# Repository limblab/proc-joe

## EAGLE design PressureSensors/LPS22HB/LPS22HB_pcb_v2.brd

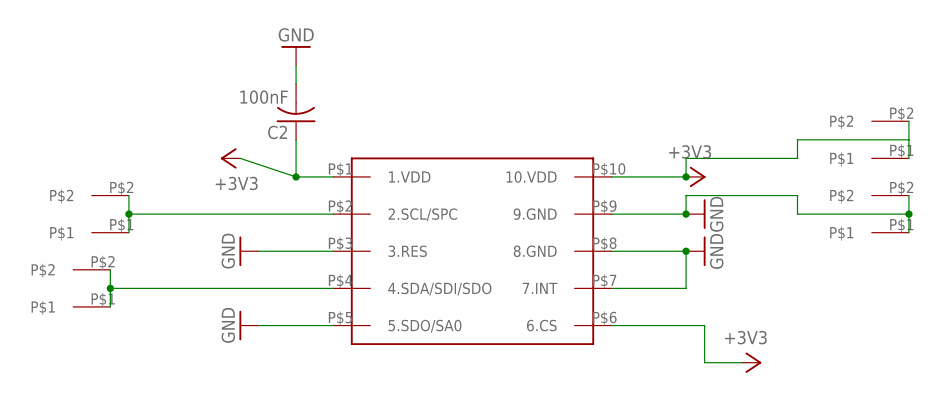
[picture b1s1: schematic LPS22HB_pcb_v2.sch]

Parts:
C2: 100nF; C0402
U$1: LPS22HB_HLGA
U$2, U$3, U$4, U$5: WIREPAD_PADWIREPAD_0,6/0,4_PAD; WIREPAD_0,6/0,4_PAD

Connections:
+3V3: C2.1, U$1.P$1 (1.VDD), U$1.P$6 (6.CS), U$1.P$10 (10.VDD), U$5.P$1, U$5.P$2
GND: C2.2, U$1.P$3 (3.RES), U$1.P$5 (5.SDO/SA0), U$1.P$7 (7.INT), U$1.P$8 (8.GND), U$1.P$9 (9.GND), U$4.P$1, U$4.P$2
unnamed: U$1.P$2 (2.SCL/SPC), U$2.P$1, U$2.P$2
unnamed: U$1.P$4 (4.SDA/SDI/SDO), U$3.P$1, U$3.P$2

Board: 2 copper layers, 6 parts (5 on the bottom side), 4 nets, no tracks yet.

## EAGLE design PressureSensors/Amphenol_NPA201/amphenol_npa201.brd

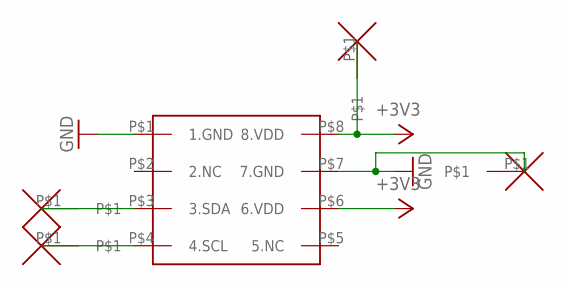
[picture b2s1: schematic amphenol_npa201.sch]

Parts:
U$1: AMPHENOL_NPA201
U$2, U$3, U$4, U$5: WIREPAD_0,8/0,45

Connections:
+3V3: U$1.P$6 (6.VDD), U$1.P$8 (8.VDD), U$4.P$1
GND: U$1.P$1 (1.GND), U$1.P$7 (7.GND), U$5.P$1
unnamed: U$1.P$3 (3.SDA), U$2.P$1
unnamed: U$1.P$4 (4.SCL), U$3.P$1

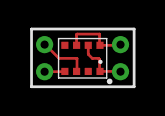
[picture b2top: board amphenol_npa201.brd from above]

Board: 2 copper layers, 5 parts (0 on the bottom side), 4 nets.

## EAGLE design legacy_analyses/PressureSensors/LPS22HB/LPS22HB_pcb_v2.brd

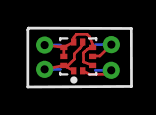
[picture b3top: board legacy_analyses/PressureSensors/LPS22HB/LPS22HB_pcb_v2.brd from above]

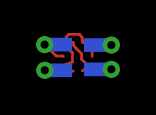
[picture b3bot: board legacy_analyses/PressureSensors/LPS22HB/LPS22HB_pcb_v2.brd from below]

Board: 2 copper layers, 5 parts (4 on the bottom side), 4 nets.

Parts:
U1: LPS22HB; LGA10R50P2X3_200X200X80
U$1, U$2, U$6, U$7: WIREPAD_PADWIREPAD_0,6/0,4_PAD; WIREPAD_0,6/0,4_PAD

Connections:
+3V3: U1.1, U1.6, U1.10, U$1.P$1, U$1.P$2
GND: U1.3, U1.5, U1.7, U1.8, U1.9, U$2.P$1, U$2.P$2
unnamed: U1.2, U$6.P$1, U$6.P$2
unnamed: U1.4, U$7.P$1, U$7.P$2

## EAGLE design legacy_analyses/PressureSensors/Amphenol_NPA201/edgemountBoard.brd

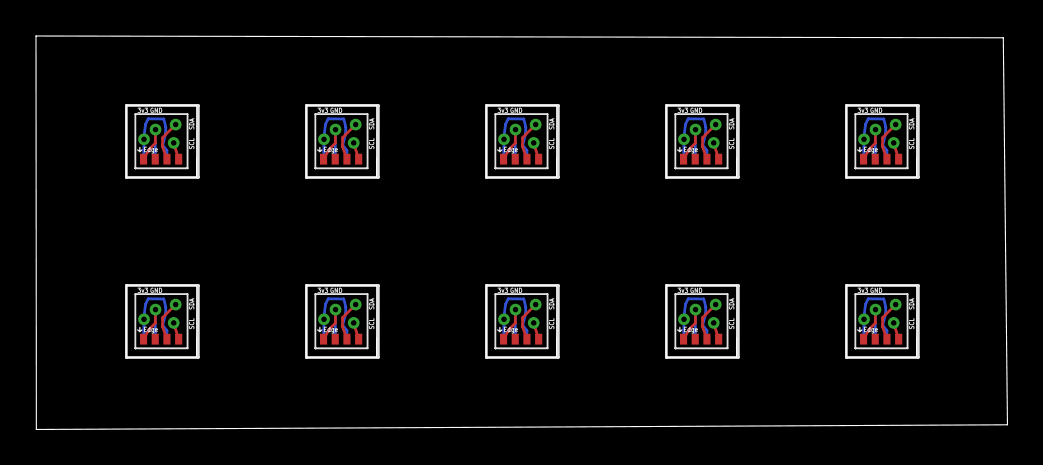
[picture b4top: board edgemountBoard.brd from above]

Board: 2 copper layers, 54.0 x 21.9 mm, 50 parts (0 on the bottom side), 40 nets.

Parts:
U$1, U$6, U$11, U$16, U$21, U$26, U$31, U$36, U$41, U$46: AMPHENOL_NPA201EDGEMOUNT; AMPHENOL_NPA201_EDGEMOUNT
U$2, U$3, U$4, U$5, U$7, U$8, U$9, U$10, U$12, U$13, U$14, U$15, U$17, U$18, U$19, U$20, U$22, U$23, U$24, U$25, U$27, U$28, U$29, U$30, U$32, U$33, U$34, U$35, U$37, U$38, U$39, U$40, U$42, U$43, U$44, U$45, U$47, U$48, U$49, U$50: WIREPADWIREPAD_0,5/0,3; WIREPAD_0,5/0,3

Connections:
+3V1: U$6.P$6, U$6.P$8, U$10.P$1
+3V2: U$11.P$6, U$11.P$8, U$15.P$1
+3V3: U$1.P$6, U$1.P$8, U$5.P$1
+3V4: U$16.P$6, U$16.P$8, U$20.P$1
+3V5: U$21.P$6, U$21.P$8, U$25.P$1
+3V6: U$26.P$6, U$26.P$8, U$30.P$1
+3V7: U$31.P$6, U$31.P$8, U$35.P$1
+3V8: U$36.P$6, U$36.P$8, U$40.P$1
+3V9: U$41.P$6, U$41.P$8, U$45.P$1
+3V10: U$46.P$6, U$46.P$8, U$50.P$1
GND: U$1.P$1, U$1.P$7, U$4.P$1
GND1: U$6.P$1, U$6.P$7, U$9.P$1
GND2: U$11.P$1, U$11.P$7, U$14.P$1
GND3: U$16.P$1, U$16.P$7, U$19.P$1
GND4: U$21.P$1, U$21.P$7, U$24.P$1
GND5: U$26.P$1, U$26.P$7, U$29.P$1
GND6: U$31.P$1, U$31.P$7, U$34.P$1
GND7: U$36.P$1, U$36.P$7, U$39.P$1
GND8: U$41.P$1, U$41.P$7, U$44.P$1
GND9: U$46.P$1, U$46.P$7, U$49.P$1
unnamed: U$1.P$3, U$2.P$1
unnamed: U$1.P$4, U$3.P$1
unnamed: U$6.P$3, U$7.P$1
unnamed: U$6.P$4, U$8.P$1
unnamed: U$11.P$3, U$12.P$1
unnamed: U$11.P$4, U$13.P$1
unnamed: U$16.P$3, U$17.P$1
unnamed: U$16.P$4, U$18.P$1
unnamed: U$21.P$3, U$22.P$1
unnamed: U$21.P$4, U$23.P$1
unnamed: U$26.P$3, U$27.P$1
unnamed: U$26.P$4, U$28.P$1
unnamed: U$31.P$3, U$32.P$1
unnamed: U$31.P$4, U$33.P$1
unnamed: U$36.P$3, U$37.P$1
unnamed: U$36.P$4, U$38.P$1
unnamed: U$41.P$3, U$42.P$1
unnamed: U$41.P$4, U$43.P$1
unnamed: U$46.P$3, U$47.P$1
unnamed: U$46.P$4, U$48.P$1

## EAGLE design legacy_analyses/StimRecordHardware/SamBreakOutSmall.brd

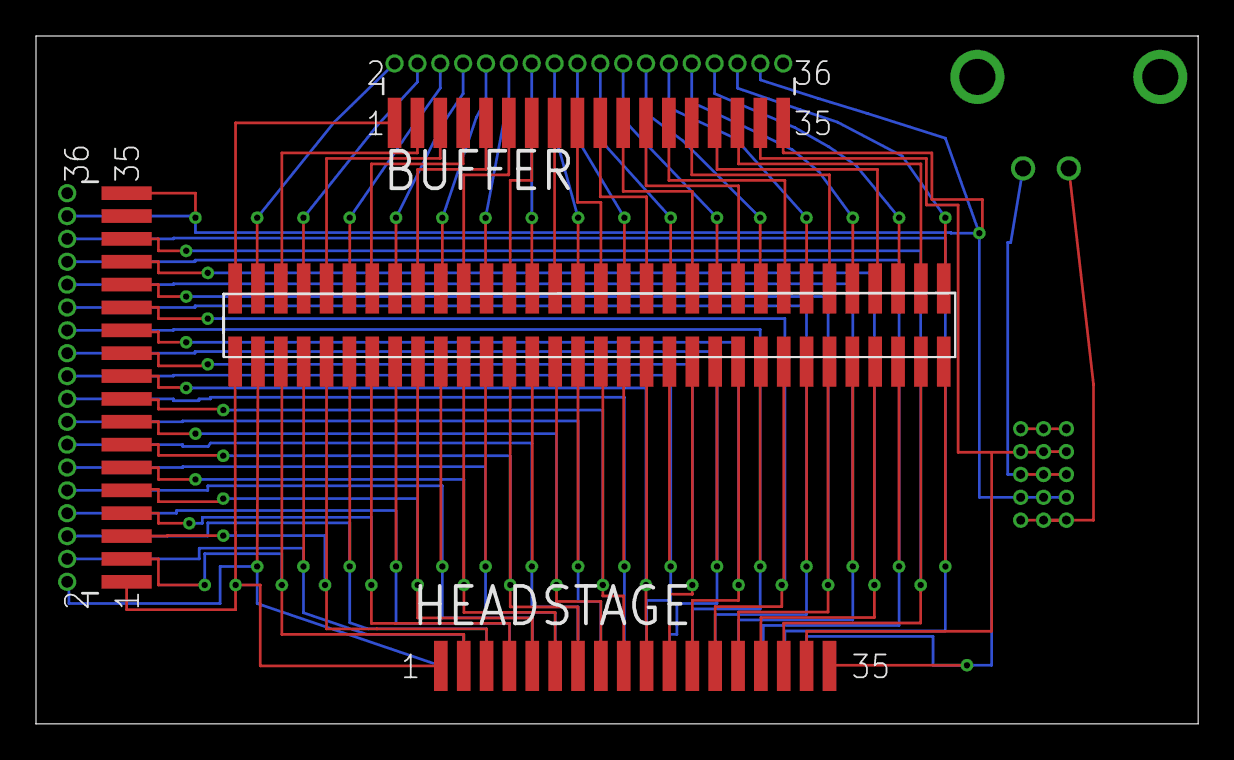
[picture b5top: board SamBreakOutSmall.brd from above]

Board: 2 copper layers, 64.6 x 38.2 mm, 8 parts (0 on the bottom side), 69 nets.

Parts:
BUFFER: FTSH-118-01-L-MTREGULAR; FTSH-118-01-L-MT
HEADSTAGE: SFMC-118-L1-S-D
STIM: FTSH-118-01-L-MTREGULAR; FTSH-118-01-L-MT
U$1: BNCRAMOUNT
U$3: FTSH-132-01-L-DV; FTSH-132-01-DV
U$34, U$35, U$36: LPPB051NFFN-RC

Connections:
0V: BUFFER.33, HEADSTAGE.33, U$34.P$2, U$35.P$2, U$36.P$2
GND: BUFFER.34, BUFFER.35, HEADSTAGE.34, HEADSTAGE.35, STIM.34, STIM.35, U$34.P$4, U$35.P$4, U$36.P$4
unnamed: BUFFER.1, U$3.2
unnamed: BUFFER.29, U$3.58
unnamed: BUFFER.3, U$3.6
unnamed: BUFFER.2, U$3.4
unnamed: BUFFER.5, U$3.10
unnamed: BUFFER.7, U$3.14
unnamed: BUFFER.9, U$3.18
unnamed: BUFFER.11, U$3.22
unnamed: BUFFER.13, U$3.26
unnamed: BUFFER.15, U$3.30
unnamed: BUFFER.17, U$3.34
unnamed: BUFFER.19, U$3.38
unnamed: BUFFER.27, U$3.54
unnamed: BUFFER.23, U$3.46
unnamed: BUFFER.25, U$3.50
unnamed: BUFFER.4, U$3.8
unnamed: BUFFER.6, U$3.12
unnamed: BUFFER.31, U$3.62
unnamed: BUFFER.8, U$3.16
unnamed: BUFFER.10, U$3.20
unnamed: BUFFER.12, U$3.24
unnamed: BUFFER.14, U$3.28
unnamed: BUFFER.16, U$3.32
unnamed: BUFFER.18, U$3.36
unnamed: BUFFER.20, U$3.40
unnamed: BUFFER.21, U$3.42
unnamed: BUFFER.22, U$3.44
unnamed: BUFFER.24, U$3.48
unnamed: BUFFER.26, U$3.52
unnamed: BUFFER.28, U$3.56
unnamed: BUFFER.30, U$3.60
unnamed: BUFFER.32, U$3.64
unnamed: HEADSTAGE.3, STIM.3, U$3.5
unnamed: HEADSTAGE.5, STIM.5, U$3.9
unnamed: HEADSTAGE.7, STIM.7, U$3.13
unnamed: HEADSTAGE.9, STIM.9, U$3.17
unnamed: HEADSTAGE.11, STIM.11, U$3.21
unnamed: HEADSTAGE.13, STIM.13, U$3.25
unnamed: HEADSTAGE.15, STIM.15, U$3.29
unnamed: HEADSTAGE.17, STIM.17, U$3.33
unnamed: HEADSTAGE.19, STIM.19, U$3.37
unnamed: HEADSTAGE.21, STIM.21, U$3.41
unnamed: HEADSTAGE.23, STIM.23, U$3.45
unnamed: HEADSTAGE.25, STIM.25, U$3.49
unnamed: HEADSTAGE.27, STIM.27, U$3.53
unnamed: HEADSTAGE.29, STIM.29, U$3.57
unnamed: HEADSTAGE.31, STIM.31, U$3.61
unnamed: HEADSTAGE.2, STIM.2, U$3.3
unnamed: HEADSTAGE.4, STIM.4, U$3.7
unnamed: HEADSTAGE.6, STIM.6, U$3.11
unnamed: HEADSTAGE.8, STIM.8, U$3.15
unnamed: HEADSTAGE.10, STIM.10, U$3.19
unnamed: HEADSTAGE.12, STIM.12, U$3.23
unnamed: HEADSTAGE.14, STIM.14, U$3.27
unnamed: HEADSTAGE.16, STIM.16, U$3.31
unnamed: HEADSTAGE.18, STIM.18, U$3.35
unnamed: HEADSTAGE.20, STIM.20, U$3.39
unnamed: HEADSTAGE.22, STIM.22, U$3.43
unnamed: HEADSTAGE.24, STIM.24, U$3.47
unnamed: HEADSTAGE.26, STIM.26, U$3.51
unnamed: HEADSTAGE.28, STIM.28, U$3.55
unnamed: HEADSTAGE.30, STIM.30, U$3.59
unnamed: HEADSTAGE.32, STIM.32, U$3.63
unnamed: HEADSTAGE.1, STIM.1, U$3.1
unnamed: U$1.1.GND, U$34.P$3, U$35.P$3, U$36.P$3
unnamed: U$34.P$1, U$35.P$1, U$36.P$1
unnamed: U$1.2.SIG, U$34.P$5, U$35.P$5, U$36.P$5

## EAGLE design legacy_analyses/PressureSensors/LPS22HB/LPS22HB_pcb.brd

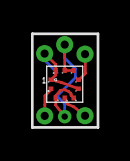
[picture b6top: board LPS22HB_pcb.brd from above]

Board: 2 copper layers, 7 parts (1 on the bottom side), 5 nets.

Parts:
C2: 100nF; C0402
U$1: LPS22HB_HLGA
U$2, U$3, U$6, U$7, U$8: WIREPAD_0,8/0,45

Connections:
+3V3: C2.1, U$1.P$1, U$1.P$6, U$1.P$10, U$8.P$1
GND: C2.2, U$1.P$3, U$1.P$5, U$1.P$8, U$1.P$9, U$7.P$1
unnamed: U$1.P$4, U$3.P$1
unnamed: U$1.P$2, U$2.P$1
unnamed: U$1.P$7, U$6.P$1

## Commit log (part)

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2017-03-15 added stimulation artifact work
2017-03-17 lots of updates
2017-03-17 fixed bugs
2017-04-26 long overdue commit
2017-06-12 fixed things in general
2017-06-12 change point analysis starter
2017-06-12 cpa again
2017-06-13 cpa and phase locking
2017-06-15 stim stuff
2017-06-16 sped up writeNev.m a bit
2017-06-17 small changes
2017-06-19 processing stim artifact data
2017-06-19 process stim artifact changes
2017-06-19 small update
2017-06-20 day changes
2017-06-27 daily changes
2017-06-29 updated stim artifact processing code
2017-06-29 analysis changes
2017-06-29 organized analysis code
2017-07-07 processing changes
2017-07-07 minor changes
2017-07-07 initial pressure sensor code
2017-07-07 smallc hanges
2017-07-07 pressure sensor stuff
2017-07-10 analysis updates
2017-07-13 middle of fixing bugs
2017-07-13 reorganized
2017-07-20 second peak probability code and minor changes
2017-07-21 CKC start
2017-07-24 pressure sensor breakout boards
2017-07-27 added plot filtered waveforms
2017-07-27 few changes
2017-07-28 whole array analysis
2017-08-02 process stim artifact changes before large scale changes
2017-08-02 more minor changes
2017-08-08 matching pursuit attempt
2017-08-08 reverting changes
2017-08-10 process code changes for testing on gob2
2017-08-16 reorganized eagle files
2017-08-22 hardware pcb files
2017-08-29 large changeS
2017-09-06 large scale analysis changes
2017-09-19 analysis changes for bum[pstim
2017-09-29 removed files
2017-11-01 home computer changes
2017-11-17 distribution analysis changes
2017-11-17 small change
2017-12-16 overdue changes
2017-12-29 overdue changes before messing with plotPSTHStim
2017-12-29 starting code base changes
2018-01-03 made data extraction faster (maybe)
2018-01-04 updating code to new options format
2018-01-19 ring reporting behavior figures
2018-01-23 added multiple bump mag analysis
2018-01-26 daily changes'
2018-02-12 update read serial to batch read
2018-03-13 beginning to clean things up
2018-03-14 cleaned some things up. Updated process artifact code to filter data and handle different stimulation scripts
2018-03-14 quick fix
2018-04-03 adding new folder
2018-04-05 population stim code
2018-04-13 removed old grid lines
2018-04-13 removed old plotHeatmap file
2018-04-18 removed a gif
2018-04-18 Updating to new processing code. This code no longer puts cds and waveformsSent together. Instead they are kept separate
2018-04-18 moved stimulation info over to a separate stuct for extractData code
2018-04-18 still adjusting code, found a timing bug with recoverPreSync and need to fix it
2018-04-19 changed extract data code to process a file at a time, this change made the whole array wrapper obselete
2018-04-19 removed whole array extract data code as change to single unit code made it obselete
2018-04-19 made the output plot square
2018-04-23 added reaction time subfolder
2018-04-23 added code to plot reach kinematics and to summarize the reaction times. Need to differentiate between cues in a later version
2018-04-25 added initial code to analyze reaction time data, removed trial data code
2018-04-26 fixed a bug in the get movement onset code
2018-04-27 changes made to reaction time code, mostly centered around how to detect movement onset
2018-04-27 changed how movement onset is found, organized code better, added a few plotting functions
2018-05-02 overdue commit to reaction time code
2018-05-04 started code conversion to trial data format
2018-05-04 changed to using trial data
2018-05-06 added std bars and a plot for all data points to reaction time code
2018-05-06 test
2018-05-06 added psychometric curve code, removed all non-TD functions
2018-05-07 added saving code to reaction time plots
2018-05-08 added code to start looking at pca and clustering of waveforms
2018-05-09 renamed stim record folder, fixed some reaction time code
2018-05-09 force stimInfo.() to be columns which fixed a bug. Daily changes otherwise
2018-05-09 added back commented lines
2018-05-09 started messing around with glm's
2018-05-14 added code to plot learning
2018-05-14 changes at home computer
2018-05-14 fixed bugs, set a rt metric that seems reasonable
2018-05-20 added ks test code to plotNumberOfSpikes
2018-05-21 started adding raster and psth plots to reaction time code
2018-05-24 added code to project acceleration onto an arbitrary target axis, also added tgtDir to trial table
2018-05-24 fixed a bug related to units coming in and out of files
2018-06-21 reaction time changes
2018-06-21 reaction time model update
2018-06-21 fixed bugs related to using 2016a instead of 2016b
2018-06-22 gob changes
2018-06-22 laptop changes
2018-06-25 fixed bugs, added support for many files with differen channels and waveforms
2018-06-25 fixed a bug related to Nan
2018-06-25 Fixed psychometric curve stim
2018-08-02 added code for 2afc (kramer) task
2018-08-02 added git ignore finally
2018-08-06 code to analyze kramer task
2018-08-22 code used for RT figures v1
2018-08-27 merging still
2018-11-09 overdue commit, changing code to work with Duncan, save state for Han
2018-12-07 simulate artifact for duke project box
2018-12-14 fixed multistim analysis code to subtract baseline firing
2018-12-20 adding folder for hardware related to the stim record project
2018-12-20 removing bunch of random files
2018-12-20 cleaning files up
2019-04-11 long overdue commit wow
2019-06-19 overdue analysis changes
2019-06-20 added rebin code to master branch
2019-07-11 bootstrapping
2019-07-11 fixed a bug, still working on bootstrapping code
2019-07-11 random changes
2019-07-12 kramer task bootstrapping changes
2019-07-12 bootstrapping updates
2019-07-12 added pse code
2019-07-12 bootstrap plot changes
2019-07-16 slope changes and other quality of life changes
2019-07-20 changed how max trial time worked
2019-07-31 anaylze trains with different time between trains
2019-08-16 removed old files and added velocity data to analyzeTrainData
2019-08-16 added force to extractData
2019-08-16 added kin data to extract spikes
2019-08-16 analyzing chan 21
2019-08-22 updated stim rec analysis code. Making large changes in the next few days so this is a good save spot
2019-08-26 looking at inhib duration code
2019-08-26 minor bug fixes
2019-08-27 fixed and updated speed code. working on train summary code
2019-09-09 gob2 overdue commit
2019-09-11 fixed bug where wrong set of parameters were loaded into TD
2019-09-24 large analysis changes
2019-09-25 fixed bug related to having more than one pulse per train
2019-09-30 multichannel stim code and some CO bump stuff
2019-10-02 undo stimInfo
2019-10-09 train and dbl pulse analysis changes
2019-10-17 standardized spike values for heatmap, created heatmap code for preferred directions
2019-10-17 omnetics breakout board v1
2019-10-18 updated pinouts of omnetics board
2019-10-24 omnetics breakout board update
2019-10-25 reorganized non stim analysis
2019-10-28 added num_trials_all to count trials across conditions
2019-10-28 deleted a few file copies. Updated plotHeatmaps to handle a single neuron and multiple stim chans, started to make combineHeatmaps a function and then stopped
2019-10-30 stability analysis upda
2019-10-30 combineHeatmaps now multiplies two 10x10 arrays instead of two 1xunits arrays, combineHeatmaps also calculates average value , started structuring combineHeatmaps and analyzeNonStimChannelData to plo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
2019-10-31 changed filenames
2019-10-31 reformatted a bunch of code
2019-11-01 updated colormap code and slopes for train data
2019-11-01 code for analyzing bias in stim channel PDs
2019-11-06 updated omnetics break out board
2019-11-07 overdue changes from home
2019-11-11 added useful helper functions for train data code
2019-11-11 organized code
2019-11-13 fixed processing bugs for long train data
2019-12-03 analysis changes for long trains
2020-01-02 long train data analysis code
2020-01-02 omentics breakout board
2020-04-15 overdue commit, stim analysis changes
2020-06-11 python datasets
2020-06-16 updated building stim patterns. Need to still consolidate that code
2020-06-29 writing code to compare experiment and model data
2020-06-29 co move bump code
2020-06-30 added code to get model data from Karthik's files and to get activation thresholds
2020-07-02 code to analyze movements due to stimulation in the center hold period
2020-07-03 added code to plot distance stim data
2020-07-06 updated activation threshold computation to account for baseline firing rate
2020-07-06 added space constant code
2020-07-06 updated code for stim dynamics project
2020-07-08 updated space constant code to handle synapse data
2020-07-08 space consatnt code uses boxplots now
2020-07-21 code to analyze peaks and latency for same channel data
2020-07-22 space constant analysis changes
2020-07-24 started adding soup model code
2020-07-24 implemented soup model, still need to test thoroughly
2020-07-24 no idea
2020-07-31 moved inhib dur code to wrapper style and added double pulse inhib code
2020-07-31 started double pulse and train data analysis code
2020-08-03 analysis updates for python projects
2020-08-25 started code to analyze stim evoked movements
2020-08-25 learning experiment analysis started
2020-09-30 reaction time onset changes
2020-11-25 toy stim column model for analyzing Karthik's data
2020-12-01 added code for DLC
2020-12-02 updated code to streamline pipeline
2020-12-07 updates to DLC pipeline
2020-12-13 updated trim_video code to hopefully remove indexing bug
2020-12-22 updated DLC pipeline
2020-12-22 updated 3D reconstruction code to handle dropouts. Need to debug still
2020-12-28 added code to sync DLC frames with neural data in the cds
2020-12-28 moved DLC code to new git folder
2021-01-05 updated code to load in free reaching data to cds and trial data. Also, last commit before some major changes to my stimrec code
2021-01-07 cleaning up stimrec code so that paper related figures are easier to produce. Currently removing heatmap plots from analyze-long-train code
2021-01-19 updated stim-paper code, also updated encoder model code for deeplabcut
2021-01-21 updated sim study for stim-rec project
2021-01-26 updated code to produce stim/rec ephys paper figures
2021-01-26 storing a version of trial data in my proc folder since I can't push code to the original repository
2021-01-29 added code to analyze reaching kinematics
2021-02-01 Minor directory and comment changes
    conflict was on line 155, number of repeats for the "reachingEncoders" function.
2021-02-09 added code to deal with PDs and to predict firing rates. Need to check PD code and deal with cross-validation still
2021-02-10 checked merge with Qiwei, fixed a small bug and am now pushing back
2021-02-10 renamed file so it had a different name than one in neuron-table, which I can't push to
2021-02-17 updated some paper scripts and 3D reaching scripts to deal with frame number bug
2021-03-22 updated code for figures and statistics for paper. v4 of results and v1-3 of figures
2021-04-12 updated code to make stim record figures
2021-04-14 add figures to plot hand position in 3D space, beginning to change figures that plot the correlation between markers
2021-04-15 improved the code for plotting example figures of hand position in space
2021-05-11 added code to plot several figures, now trying to change the input of the model from V + Position to V OR Position
2021-05-27 add figures in freereaching_analysis.m and reachingKinematics.m, add a if-else statement that differentiates Han and Crackle's shoulder names in setOriginAsShoulder.m, implemented getExperimentPhase.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
2021-05-27 deleted fig10 (one of the worse pR2 figures), and fig 9. Fixed fig 8.
2021-05-27 overdue stim rec commit
2021-05-28 updated figure names
2021-06-04 updated getExperimentPhase and some analyses
2021-07-12 added code to analyze data for 3D reaching weight experiment. This code should be combined with the free reaching code at some point
2021-07-14 removed excess code from freereaching_analysis
2022-02-04 overdue commit, many changes for the stim-rec paper and the stim-vae simulations
2022-02-18 v1 of code to subsample DLC training frames based on similarity
